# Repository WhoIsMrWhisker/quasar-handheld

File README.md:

<body>

<h1 align="center">Quasar Handheld🌠</h1>

### ⚠️Status information 
The project is still under development and it's not made yet, expect software after full hardware development.

## ❓ About the device
An advanced, custom-engineered handheld platform utilizing a dual-MCU architecture. The project breaks away from standard single-processor limitations by combining the high-speed wireless capabilities of the ESP32 with the robust, real-time hardware co-processing of an STM32. 

## 🚀 System Architecture & Features
* **Dual-MCU Core:** Features an ESP32 for Wi-Fi/Bluetooth connectivity and main applications, paired with an STM32 co-processor managing low-level hardware routines.
* **Optimized Audio Block:** Integrates an 8-pin digital I2S audio decoder chip, completely replacing bulky legacy analog components (aux jacks, power transistors, protection diodes) with a clean, low-noise digital audio path.
* **Peripherals & I/O:** Complete integration of a display module, dedicated power management/battery circuitry, and high-speed communication lines linking both processors.

## 🛠️ Hardware Stack
* **Main Compute:** ESP32-S3-MINI-1U
* **Co-Processor:** STM32F405RGT6 **Can be accessible via UART or SPI Slave**
* **Audio:** 8 ohm speaker that is managed by D-Class MAX98357A DAC Audio amplifier and Integrated CPT-9019S-SMT-TR Buzzer 
* **PCB Constraints:** 4-Layers, optimized ground plane return paths
* **Power delivery and management:** Uses MAX17260SETD+ Fuel gauge, TP4056 Battery chip charger, AP2112K-3.3 LDO regulator and TPS22917DBVR Load switch.
* **Memory addons:** W25Q128JVS 16kb SPI Flash for secondary firmware and shared APS6404L-SQRx-SN series shared SRAM
* **Haptics and Microphone:** ERM Haptic engine with flyback diode for protection, and MAX9814 Microphone amplifier
* **Display:** TFT SPI ST7789 Colorful Display
* **Gyroscope:** MPU-6050 Chip
* **GPS Navigation:** Ai-Thinker GP-02 GPS module
* **Extension ports:** One USART port 
* **USB Interface:** Uses two receptacle 16 pin USB, one for ESP32 + Charging, second is for STM32 ⚠️**DATA ONLY**
* **Radio things:** Ra-01, NRF24L01, Si4735-D60-GU
* **RFID/NFC:** PN532 with balun transformer (50 ohm coaxial)

* **Note to radio connectors:** I use U.Fl IPEX-1 SMA, and (Hirose SMT-1 Vertical) and also Amphenol 132289 EdgeMount Female SMA connector (use 2.4ghz FPC patches for ESP32-S3-MINI-1U and NRF24l01, 13.56MHZ for RFID and GPRS FPC antenna, or use U.FL to SMA connector, use anything as long if it's 50 ohm connector.)

## 💫 Credits
Thanks to JLCPCB, KiCad i can make this project come true⭐.
And thanks to my teacher that teached the basis of electronics: [Maxym Kaplun](https://github.com/KaplunMaxym).

## 📈 Working on
* Polishing up the board

## ⚖️ Licensing
This project is licensed under the **Creative Commons Attribution-NonCommercial-ShareAlike 4.0 International (CC BY-NC-SA 4.0)** license. 

You are welcome to download, study, and modify these design files for personal or educational use. However, **commercial use, mass production, or selling the physical PCBs/assembled units is strictly prohibited** without explicit permission, and also fork this project with my license because of SA.
</body>

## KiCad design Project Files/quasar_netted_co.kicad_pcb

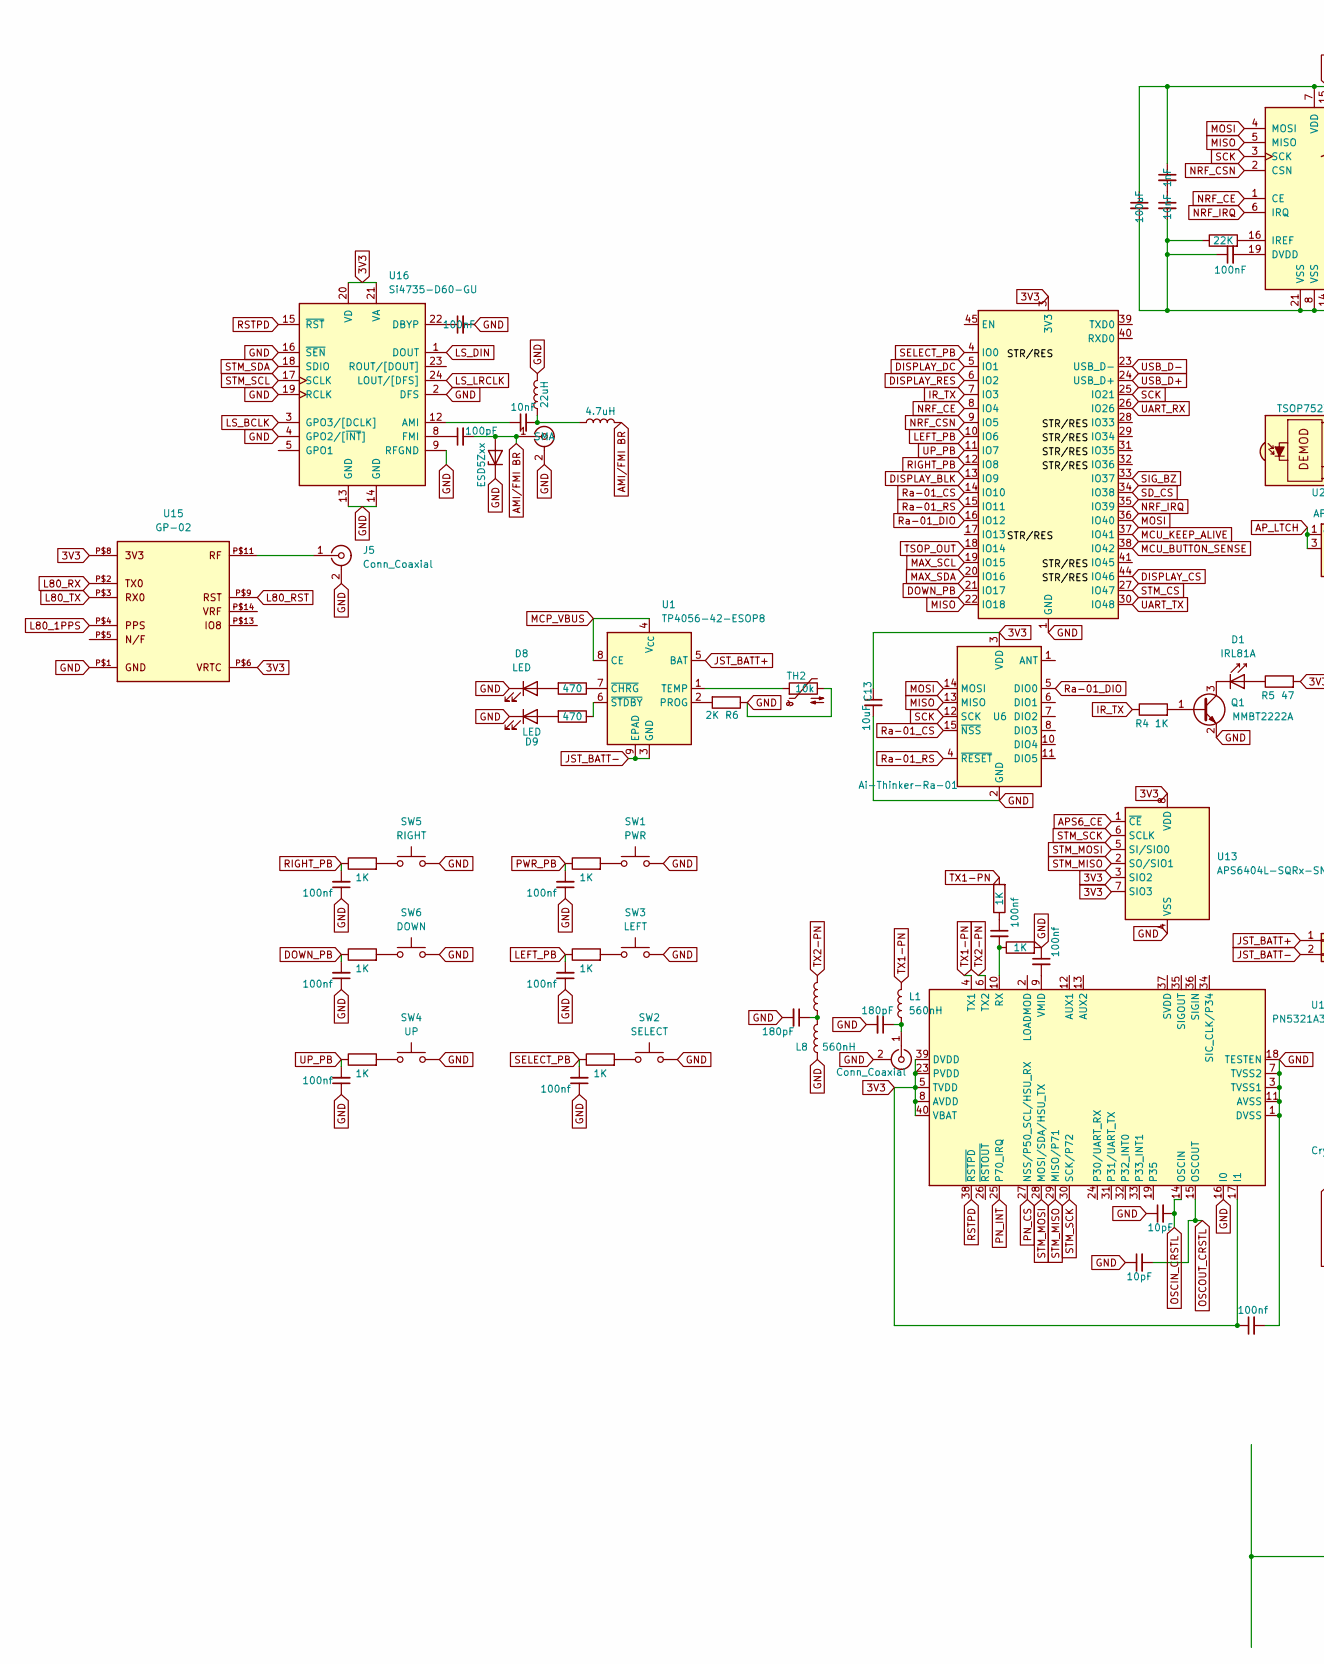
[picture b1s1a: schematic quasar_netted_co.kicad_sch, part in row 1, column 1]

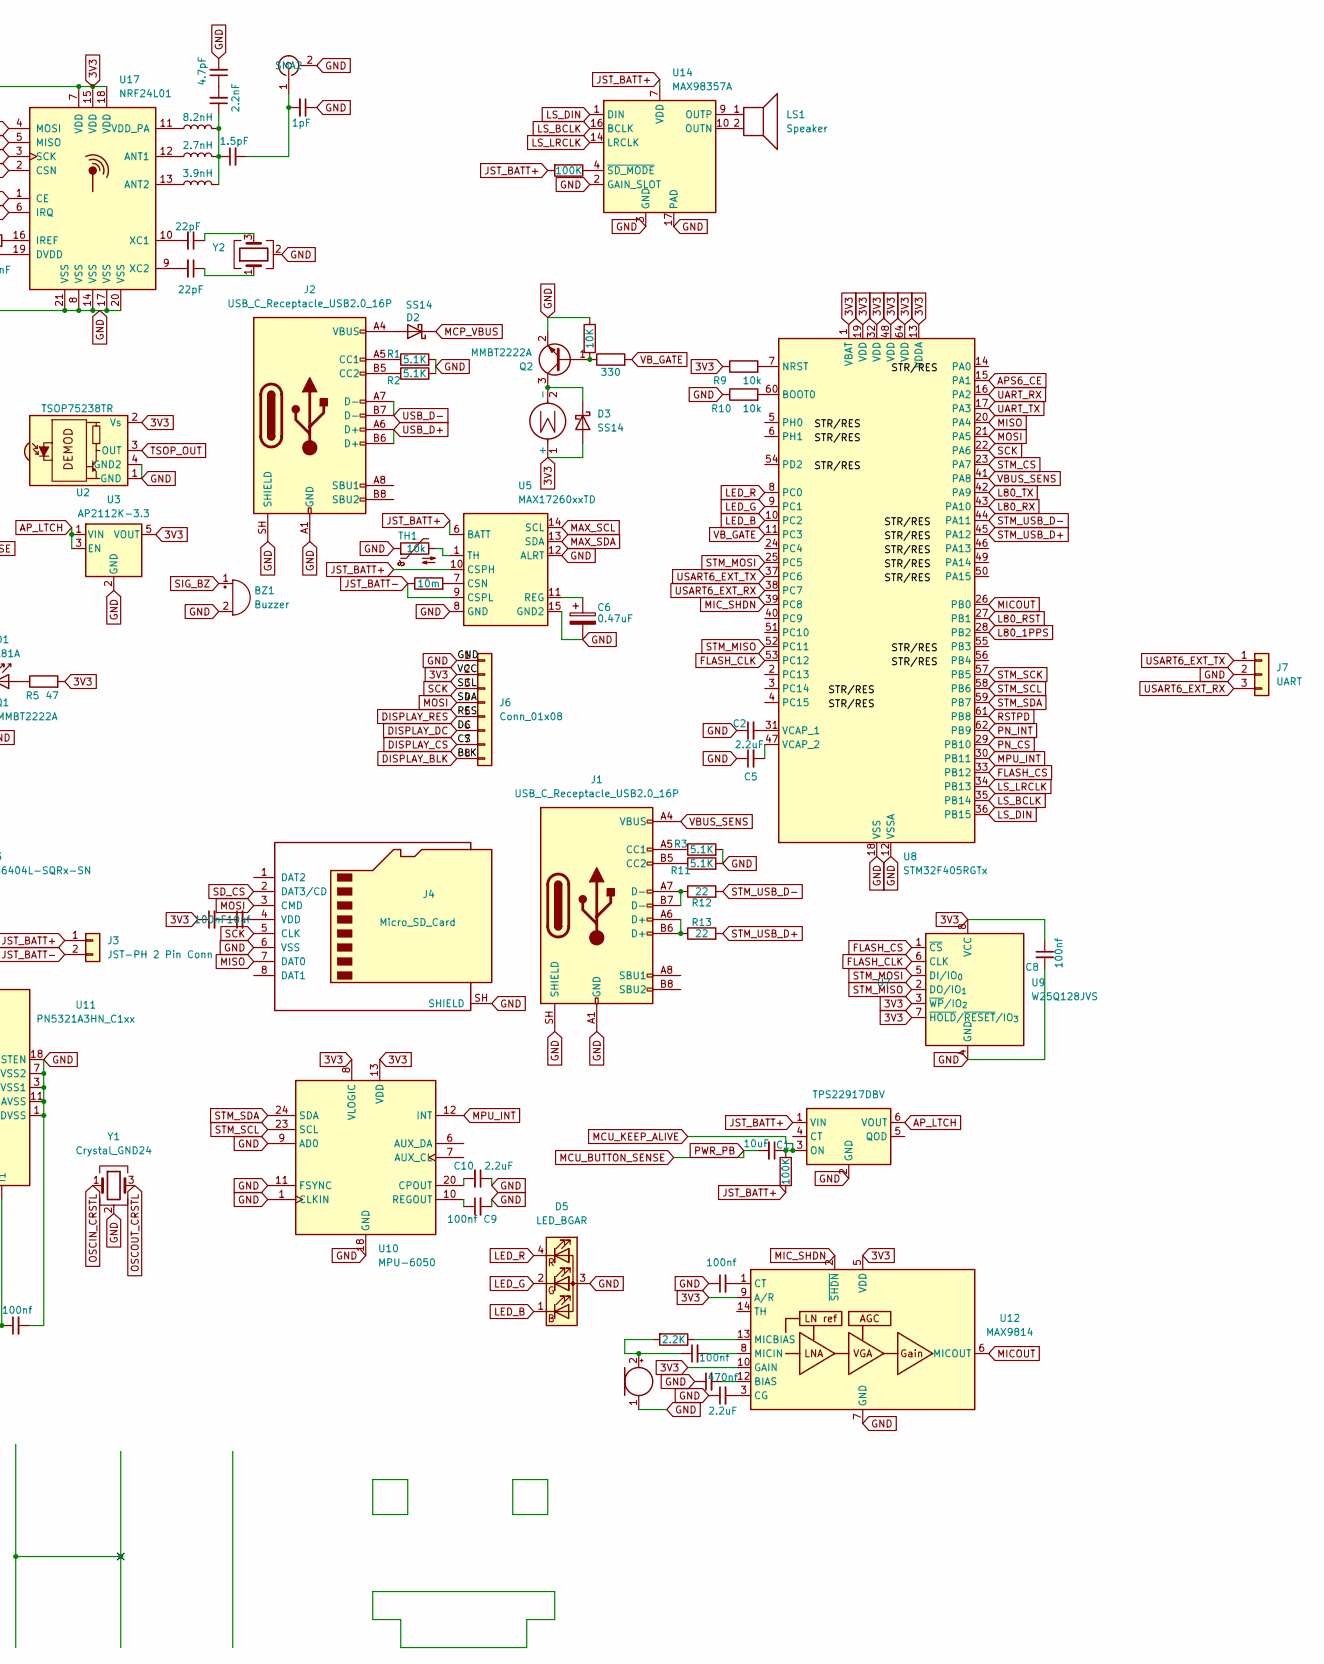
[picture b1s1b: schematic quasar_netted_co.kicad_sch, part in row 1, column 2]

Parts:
BZ1: Buzzer; Buzzer_CUI_CPT-9019S-SMT
C1, C13: 10uF; C_0805_2012Metric
C2, C5, C10, C20: 2.2uF; C_0805_2012Metric
C4: 10uf; C_0805_2012Metric
C6: 0.47uF; C_0805_2012Metric
C7, C23, C38: 100nF; C_0805_2012Metric
C8, C9, C14, C16, C18, C19, C21, C26, C27, C28, C29, C30, C31: 100nf; C_0805_2012Metric
C11, C12: 10pF; C_0805_2012Metric
C15, C17: 180pF; C_0805_2012Metric
C22: 470nf; C_0805_2012Metric
C24, C25: 22pF; C_0805_2012Metric
C32, C41: 10nF; C_0805_2012Metric
C33: 1nF; C_0805_2012Metric
C34: 1.5pF; C_0805_2012Metric
C35: 1pF; C_0805_2012Metric
C36: 2.2nF; C_0805_2012Metric
C37: 4.7pF; C_0805_2012Metric
C39: 100uF; C_0805_2012Metric
C40: 100pF; C_0805_2012Metric
D1: IRL81A; LED_Kingbright_APFA3010_3x1.5mm_Horizontal
D2, D3: SS14; D_SMA
D5: LED_BGAR; LED_D5.0mm-4_RGB
D6: ESD5Zxx; D_SOD-523
D8, D9: LED; LED_0805_2012Metric
J1, J2: USB_C_Receptacle_USB2.0_16P; USB_C_Receptacle_GCT_USB4105-xx-A_16P_TopMnt_Horizontal
J3: JST-PH 2 Pin Conn; JST_GH_SM02B-GHS-TB_1x02-1MP_P1.25mm_Horizontal
J4: Micro_SD_Card; microSD_HC_Hirose_DM3BT-DSF-PEJS
J5, J13: Conn_Coaxial; U.FL_Hirose_U.FL-R-SMT-1_Vertical
J6: Conn_01x08; PinSocket_1x08_P2.54mm_Vertical
J7: UART; PinSocket_1x03_P2.54mm_Horizontal
J11: SMA2; U.FL_Hirose_U.FL-R-SMT-1_Vertical
J12: SMA; SMA_Amphenol_132289_EdgeMount
L1, L2, L8: 560nH; L_0805_2012Metric
L3: 2.7nH; L_0805_2012Metric
L4: 3.9nH; L_0805_2012Metric
L5: 8.2nH; L_0805_2012Metric
L6: 22uH; L_0805_2012Metric
L7: 4.7uH; L_0805_2012Metric
LS1: Speaker; TestPoint_2Pads_Pitch2.54mm_Drill0.8mm
M1: Motor_DC; TestPoint_2Pads_Pitch2.54mm_Drill0.8mm
MK1: Microphone; TestPoint_2Pads_Pitch2.54mm_Drill0.8mm
Q1, Q2: MMBT2222A; SOT-23
R1, R2, R3, R11: 5.1K; R_0805_2012Metric
R4, R15, R20, R21, R22, R23, R24, R25, R29: 1K; R_0805_2012Metric
R5: 47; R_0805_2012Metric
R6: 2K; R_0805_2012Metric
R7: 10m; R_0805_2012Metric
R8: 22K; R_0805_2012Metric
R9, R10: 10k; R_0805_2012Metric
R12, R13: 22; R_0805_2012Metric
R17: 330; R_0805_2012Metric
R18: 10K; R_0805_2012Metric
R19: 2.2K; R_0805_2012Metric
R26, R27: 100K; R_0805_2012Metric
R30, R31: 470; R_0805_2012Metric
SW1: PWR; SW_PUSH_6mm_H8mm
SW2: SELECT; SW_PUSH_6mm_H8mm
SW3: LEFT; SW_PUSH_6mm_H8mm
SW4: UP; SW_PUSH_6mm_H8mm
SW5: RIGHT; SW_PUSH_6mm_H8mm
SW6: DOWN; SW_PUSH_6mm_H8mm
TH1, TH2: 10k; R_0805_2012Metric
U1: TP4056-42-ESOP8; SOIC-8-1EP_3.9x4.9mm_P1.27mm_EP2.41x3.3mm_ThermalVias
U2: TSOP75238TR
U3: AP2112K-3.3; SOT-23-5
U4: ESP32-S3-MINI-1U; ESP32-S2-MINI-1U
U5: MAX17260xxTD; TDFN-14-1EP_3x3mm_P0.4mm_EP1.78x2.35mm
U6: Ai-Thinker-Ra-01; Ai-Thinker-Ra-01-LoRa
U7: TPS22917DBV; SOT-23-6
U8: STM32F405RGTx; LQFP-64_10x10mm_P0.5mm
U9: W25Q128JVS; SOIC-8_5.3x5.3mm_P1.27mm
U10: MPU-6050; InvenSense_QFN-24_4x4mm_P0.5mm
U11: PN5321A3HN_C1xx; HVQFN-40-1EP_6x6mm_P0.5mm_EP4.1x4.1mm
U12: MAX9814; DFN-14-1EP_3x3mm_P0.4mm_EP1.78x2.35mm
U13: APS6404L-SQRx-SN; SOIC-8_3.9x4.9mm_P1.27mm
U14: MAX98357A; TQFN-16-1EP_3x3mm_P0.5mm_EP1.23x1.23mm
U15: GP-02; GP-02_FULL_PAD
U16: Si4735-D60-GU; SSOP-24_3.9x8.7mm_P0.635mm
U17: NRF24L01; QFN-20-1EP_4x4mm_P0.5mm_EP2.5x2.5mm
Y1, Y2: Crystal_GND24; Crystal_SMD_3225-4Pin_3.2x2.5mm

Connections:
3V3: C7.1, C8.1, C13.1, C19.1, C33.1, C39.1, D3.2 (A), J6.2, M1.1 (+), R5.2, R9.1, U2.2 (Vs), U3.5 (VOUT), U4.3 (3V3), U6.3 (VDD), U8.1 (VBAT), U8.13 (VDDA), U8.19 (VDD), U8.32 (VDD), U8.48 (VDD), U8.64 (VDD), U9.3 (~WP/IO_{2}), U9.7 (~HOLD/~RESET/IO_{3}), U9.8 (VCC), U10.8 (VLOGIC), U10.13 (VDD), U11.5 (TVDD), U11.8 (AVDD), U11.17 (I1), U11.23 (PVDD), U11.39 (DVDD), U11.40 (VBAT), U12.5 (VDD), U12.9 (A/R), U12.10 (GAIN), U13.3 (SIO2), U13.8 (VDD), U15.P$6, U15.P$8, U16.20 (VD), U16.21 (VA), U17.7 (VDD), U17.15 (VDD), U17.18 (VDD)
AMI/FMI BR: C40.2, D6.2 (A), J12.1 (In), L7.2
APS6_CE: U8.15 (PA1), U13.1 (~CE)
AP_LTCH: U3.1 (VIN), U3.3 (EN), U7.6 (VOUT)
DISPLAY_BLK: J6.8, U4.13 (IO9)
DISPLAY_CS: J6.7, U4.44 (IO46)
DISPLAY_DC: J6.6, U4.5 (IO1)
DISPLAY_RES: J6.5, U4.6 (IO2)
DOWN_PB: C30.2, R20.1, U4.21 (IO17)
FLASH_CLK: U8.53 (PC12), U9.6 (CLK)
FLASH_CS: U8.33 (PB12), U9.1 (~CS)
GND: BZ1.2 (-), C2.1, C5.1, C6.2, C8.2, C9.2, C10.1, C11.1, C12.1, C13.2, C14.1, C15.2, C17.2, C18.1, C19.2, C20.1, C22.1, C23.2, C26.1, C27.1, C28.1, C29.1, C30.1, C31.1, C32.2, C35.1, C37.2, C38.1, C39.2, D5.3 (A), D6.1 (K), D8.1 (K), D9.1 (K), J1.A1 (GND), J1.A12 (GND), J1.B1 (GND), J1.B12 (GND), J1.SH (SHIELD), J2.A1 (GND), J2.A12 (GND), J2.B1 (GND), J2.B12 (GND), J2.SH (SHIELD), J4.6 (VSS), J4.SH (SHIELD), J5.2 (Ext), J6.1, J7.2, J11.2 (Ext), J12.2 (Ext), J13.2 (Ext), L6.2, L8.1, MK1.1 (-), Q1.2 (E), Q2.2 (E), R1.2, R2.2, R3.2, R6.1, R8.1, R10.1, R11.2, R15.2, R18.1, SW1.2, SW2.2, SW3.2, SW4.2, SW5.2, SW6.2, TH1.1, TH2.2, U2.1 (GND), U2.4 (GND2), U3.2 (GND), U4.1 (GND), U4.2 (GND), U4.42 (GND), U4.43 (GND), U4.46 (GND), U4.47 (GND), U4.48 (GND), U4.49 (GND), U4.50 (GND), U4.51 (GND), U4.52 (GND), U4.53 (GND), U4.54 (GND), U4.55 (GND), U4.56 (GND), U4.57 (GND), U4.58 (GND), U4.59 (GND), U4.60 (GND), U4.61 (GND), U4.62 (GND), U4.63 (GND), U4.64 (GND), U4.65 (GND), U5.8 (GND), U5.12 (ALRT), U5.15 (GND2), U6.2 (GND), U6.9 (GND), U6.16 (GND), U7.2 (GND), U8.12 (VSSA), U8.18 (VSS), U8.63 (VSS), U9.4 (GND), U10.1 (CLKIN), U10.9 (AD0), U10.11 (FSYNC), U10.18 (GND), U11.1 (DVSS), U11.3 (TVSS1), U11.7 (TVSS2), U11.11 (AVSS), U11.16 (I0), U11.18 (TESTEN), U11.41 (AVSS), U12.4 (GND), U12.7 (GND), U12.11 (GND), U12.15 (GND), U13.4 (VSS), U14.2 (GAIN_SLOT), U14.3 (GND), U14.11 (GND), U14.15 (GND), U14.17 (PAD), U15.P$1, U15.P$10, U15.P$12, U16.2 (DFS), U16.4 (GPO2/[~INT]), U16.9 (RFGND), U16.13 (GND), U16.14 (GND), U16.16 (~SEN), U16.19 (RCLK), U17.8 (VSS), U17.14 (VSS), U17.17 (VSS), U17.20 (VSS), U17.21 (VSS), Y1.2 (G), Y1.4 (G), Y2.2 (G), Y2.4 (G)
IR_TX: R4.1, U4.7 (IO3)
JST_BATT+: J3.1, R26.1, R27.2, U1.5 (BAT), U5.6 (BATT), U5.10 (CSPH), U7.1 (VIN), U14.7 (VDD), U14.8 (VDD)
JST_BATT-: J3.2, R7.1, U1.3 (GND), U1.9 (EPAD), U5.9 (CSPL)
L80_1PPS: U8.28 (PB2), U15.P$4
L80_RST: U8.27 (PB1), U15.P$9
L80_RX: U8.43 (PA10), U15.P$2
L80_TX: U8.42 (PA9), U15.P$3
LED_B: D5.1 (BK), U8.10 (PC2)
LED_G: D5.2 (GK), U8.9 (PC1)
LED_R: D5.4 (RK), U8.8 (PC0)
LEFT_PB: C29.2, R22.1, U4.10 (IO6)
LS_BCLK: U8.35 (PB14), U14.16 (BCLK), U16.3 (GPO3/[DCLK])
LS_DIN: U8.36 (PB15), U14.1 (DIN), U16.1 (DOUT)
LS_LRCLK: U8.34 (PB13), U14.14 (LRCLK), U16.24 (LOUT/[DFS])
MAX_SCL: U4.19 (IO15), U5.14 (SCL)
MAX_SDA: U4.20 (IO16), U5.13 (SDA)
MCP_VBUS: D2.1 (K), U1.4 (V_{CC}), U1.8 (CE)
MCU_BUTTON_SENSE: C1.2, C31.2, R21.1, U4.38 (IO42)
MCU_KEEP_ALIVE: C1.1, R26.2, U4.37 (IO41), U7.3 (ON)
MICOUT: U8.26 (PB0), U12.6 (MICOUT)
MIC_SHDN: U8.39 (PC8), U12.2 (~SHDN)
MISO: J4.7 (DAT0), U4.22 (IO18), U6.13 (MISO), U8.20 (PA4), U17.5 (MISO)
MOSI: J4.3 (CMD), J6.4, U4.36 (IO40), U6.14 (MOSI), U8.21 (PA5), U17.4 (MOSI)
MPU_INT: U8.30 (PB11), U10.12 (INT)
NRF_CE: U4.8 (IO4), U17.1 (CE)
NRF_CSN: U4.9 (IO5), U17.2 (CSN)
NRF_IRQ: U4.35 (IO39), U17.6 (IRQ)
unnamed: C4.1, C7.2
unnamed: C16.1, R29.1
unnamed: C17.1, L2.1, L8.2
unnamed: C24.1, Y2.3
unnamed: C25.1, Y2.1
unnamed: C32.1, C33.2
unnamed: C34.1, C36.1, L3.2, L4.2, L5.2
unnamed: C36.2, C37.1
unnamed: C41.2, L6.1, L7.1
unnamed: D1.2 (A), R5.1
unnamed: D1.1 (K), Q1.3 (C)
unnamed: D2.2 (A), J2.A4 (VBUS), J2.A9 (VBUS), J2.B4 (VBUS), J2.B9 (VBUS)
unnamed: D3.1 (K), M1.2 (-), Q2.3 (C)
unnamed: D8.2 (A), R30.2
unnamed: D9.2 (A), R31.2
unnamed: J1.A5 (CC1), R3.1
unnamed: J1.B5 (CC2), R11.1
unnamed: J1.A6 (D+), J1.B6 (D+), R13.1
unnamed: J1.A7 (D-), J1.B7 (D-), R12.1
unnamed: J2.A5 (CC1), R1.1
unnamed: J2.B5 (CC2), R2.1
unnamed: C4.2, J4.4 (VDD)
unnamed: J5.1 (In), U15.P$11
unnamed: C34.2, C35.2, J11.1 (In)
unnamed: C15.1, J13.1 (In), L1.1
unnamed: C21.1, MK1.2 (+), R19.2
unnamed: Q1.1 (B), R4.2
unnamed: Q2.1 (B), R17.1, R18.2
unnamed: R20.2, SW6.1
unnamed: R21.2, SW1.1
unnamed: R22.2, SW3.1
unnamed: R23.2, SW2.1
unnamed: R24.2, SW4.1
unnamed: R25.2, SW5.1
unnamed: R6.2, U1.2 (PROG)
unnamed: TH2.1, U1.1 (TEMP)
unnamed: R30.1, U1.7 (~CHRG)
unnamed: R31.1, U1.6 (~STDBY)
unnamed: R7.2, U5.7 (CSN)
unnamed: C6.1, U5.11 (REG)
unnamed: TH1.2, U5.1 (TH)
unnamed: R10.2, U8.60 (BOOT0)
unnamed: R9.2, U8.7 (NRST)
unnamed: C2.2, U8.31 (VCAP_1)
unnamed: C5.2, U8.47 (VCAP_2)
unnamed: C10.2, U10.20 (CPOUT)
unnamed: C9.1, U10.10 (REGOUT)
unnamed: C16.2, R15.1, U11.10 (RX)
unnamed: C18.2, U11.9 (VMID)
unnamed: C22.2, U12.12 (BIAS)
unnamed: C20.2, U12.3 (CG)
unnamed: C14.2, U12.1 (CT)
unnamed: R19.1, U12.13 (MICBIAS)
unnamed: C21.2, U12.8 (MICIN)
unnamed: LS1.2, U14.10 (OUTN)
unnamed: LS1.1, U14.9 (OUTP)
unnamed: R27.1, U14.4 (~SD_MODE)
unnamed: C41.1, U16.12 (AMI)
unnamed: C23.1, U16.22 (DBYP)
unnamed: C40.1, U16.8 (FMI)
unnamed: L3.1, U17.12 (ANT1)
unnamed: L4.1, U17.13 (ANT2)
unnamed: C38.2, U17.19 (DVDD)
unnamed: R8.2, U17.16 (IREF)
unnamed: L5.1, U17.11 (VDD_PA)
unnamed: C24.2, U17.10 (XC1)
unnamed: C25.2, U17.9 (XC2)
OSCIN_CRSTL: C11.2, U11.14 (OSCIN), Y1.1
OSCOUT_CRSTL: C12.2, U11.15 (OSCOUT), Y1.3
PN_CS: U8.29 (PB10), U11.27 (NSS/P50_SCL/HSU_RX)
PN_INT: U8.62 (PB9), U11.25 (P70_IRQ)
RIGHT_PB: C28.2, R25.1, U4.12 (IO8)
RSTPD: U8.61 (PB8), U11.38 (~RSTPD), U16.15 (~RST)
Ra-01_CS: U4.14 (IO10), U6.15 (~NSS)
Ra-01_DIO: U4.16 (IO12), U6.5 (DIO0)
Ra-01_RS: U4.15 (IO11), U6.4 (~RESET)
SCK: J4.5 (CLK), J6.3, U4.25 (IO21), U6.12 (SCK), U8.22 (PA6), U17.3 (SCK)
SD_CS: J4.2 (DAT3/CD), U4.34 (IO38)
SELECT_PB: C26.2, R23.1, U4.4 (IO0)
SIG_BZ: BZ1.1 (+), U4.33 (IO37)
STM_CS: U4.27 (IO47), U8.23 (PA7)
STM_MISO: U8.52 (PC11), U9.2 (DO/IO_{1}), U11.29 (MISO/P71), U13.2 (SO/SIO1)
STM_MOSI: U8.25 (PC5), U9.5 (DI/IO_{0}), U11.28 (MOSI/SDA/HSU_TX), U13.5 (SI/SIO0)
STM_SCK: U8.57 (PB5), U11.30 (SCK/P72), U13.6 (SCLK)
STM_SCL: U8.58 (PB6), U10.23 (SCL), U16.17 (SCLK)
STM_SDA: U8.59 (PB7), U10.24 (SDA), U16.18 (SDIO)
STM_USB_D+: R13.2, U8.45 (PA12)
STM_USB_D-: R12.2, U8.44 (PA11)
TSOP_OUT: U2.3 (OUT), U4.18 (IO14)
TX1-PN: L1.2, R29.2, U11.4 (TX1)
TX2-PN: L2.2, U11.6 (TX2)
UART_RX: U4.26 (IO26), U8.16 (PA2)
UART_TX: U4.30 (IO48), U8.17 (PA3)
UP_PB: C27.2, R24.1, U4.11 (IO7)
USART6_EXT_RX: J7.3, U8.38 (PC7)
USART6_EXT_TX: J7.1, U8.37 (PC6)
USB_D+: J2.A6 (D+), J2.B6 (D+), U4.24 (USB_D+)
USB_D-: J2.A7 (D-), J2.B7 (D-), U4.23 (USB_D-)
VBUS_SENS: J1.A4 (VBUS), J1.A9 (VBUS), J1.B4 (VBUS), J1.B9 (VBUS), U8.41 (PA8)
VB_GATE: R17.2, U8.11 (PC3)

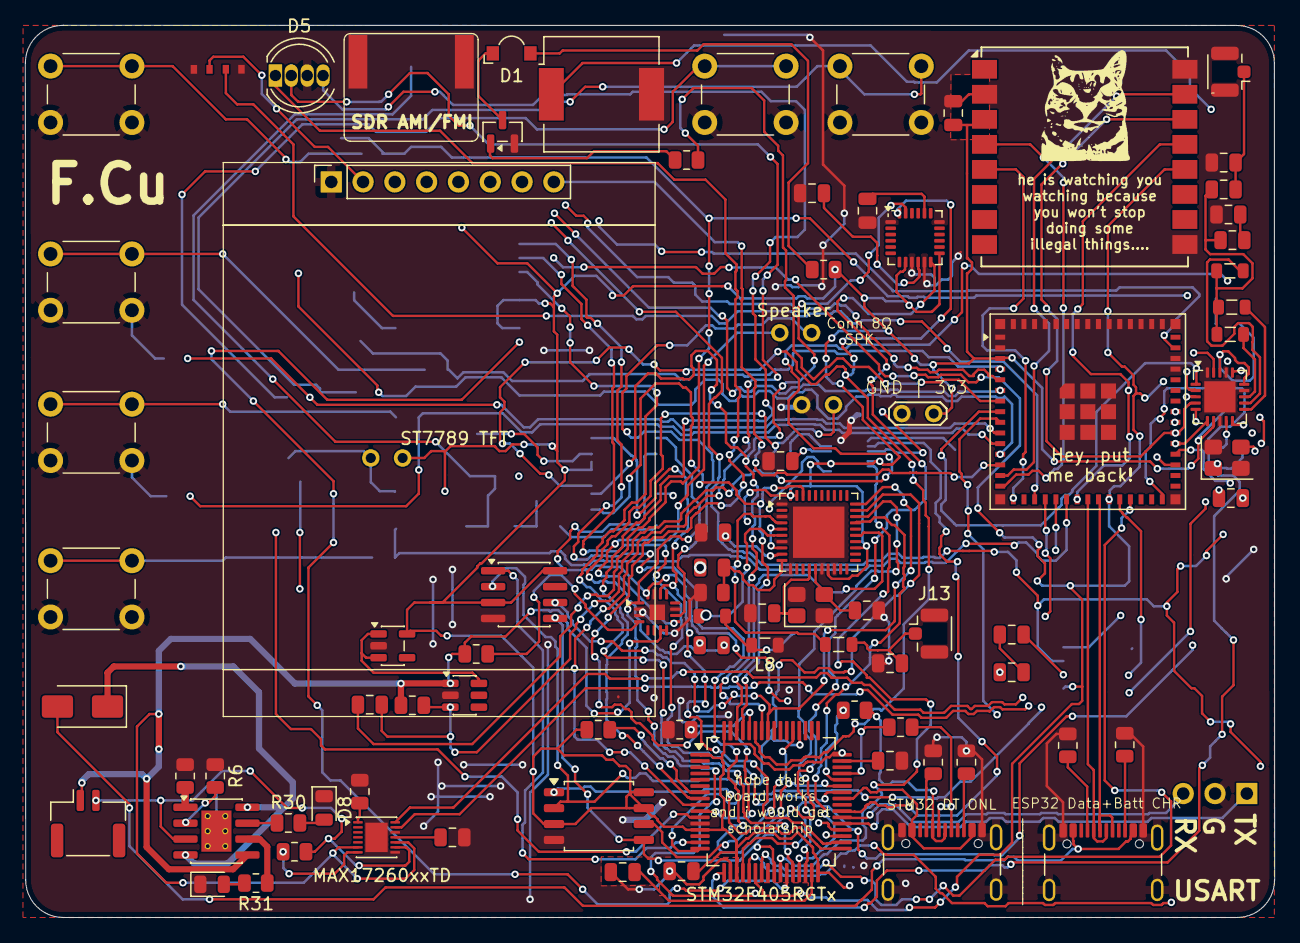
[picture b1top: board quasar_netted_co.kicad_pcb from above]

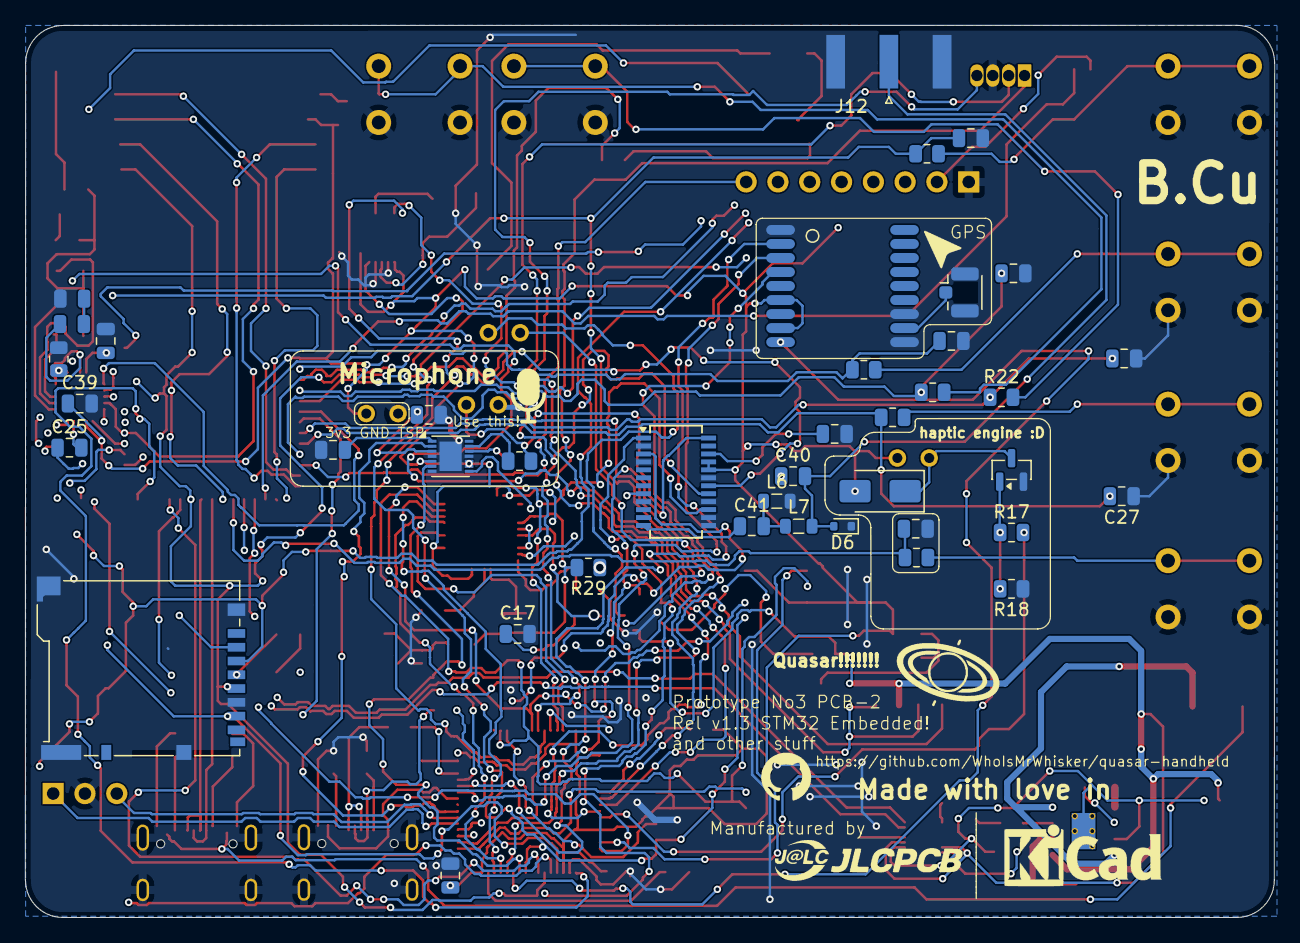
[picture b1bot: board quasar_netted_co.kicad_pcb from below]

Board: 4 copper layers, 99.8 x 71.3 mm, 127 parts (43 on the bottom side), 139 nets.

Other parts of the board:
logo: LOGO
